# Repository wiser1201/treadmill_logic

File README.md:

# Description

This project replaces the entire logic/control section of a broken treadmill with a custom-designed **STM32** microcontroller-based control system. The power electronic part of the original board stayed intact, but the control MCU and interface electronics were redesigned to restore full functionality and improve usability. Firmware is written in **C** using **HAL** library and register access when needed.

# Hardware

### Components

- **Power PCB:** Reused robust power part of the original board;
- **Logic PCB:** Designed board that contains low-voltage supply + control logic;
- **Interface PCB:** Contains three buttons, and LCD 16x2;
- **MCU:** STM32 F103C6T6;

### Architecture

System uses phase angle control topology. The original power board contains an optocoupler that triggers a triac driving the 220 VAC power rail. After each zero-cross event, the triac naturally turns off; the moment at which it is fired determines what portion of each AC half-wave reaches the motor.

The logic PCB generates a zero-cross pulse using a transformer (13 VAC), rectifier, and an optocoupler. When the AC waveform rises above the LED threshold (~1.2 V), the optocoupler produces a clean pulse that marks each zero-crossing. STM32 receives this pulse, TIM1 in one pulse slave mode starts counting a delay automatically, and then, in the end of the delay, fires a short trigger pulse to the power-stage optocoupler, which in turn fires the main triac.

Motor speed is closed-loop controlled. The PID controller adjusts delay of TIM1 based on the current speed, calculated via RPM and a belt length. If current speed lower than target, PID decreases TIM1 delay, that gives more power to the triac. And vice versa.

# Software

### Architecture

Almost all software is divided into two layers: driver and application. 

- **Driver layer.** Low level code related to peripheral configuration, peripheral initialization.

- **Application layer.** Code, that's not related or not only related to peripherals. Software that built on top of the drivers, and corresponds to one specific use.

Some modules (such as simple Buttons or Buzzer) are too small to justify a strict driver/application separation. In these cases, the functionality is implemented in a single combined module to keep the code clean and avoid unnecessary fragmentation.

### Main loop

The main loop coordinates the system's high-level tasks: motion control, fault monitoring, button handling**, **buzzer control, and LCD updates:

- **motion.** Executes the PID-based speed control described earlier, updating the phase-angle delay according to the current RPM feedback.
- **fault_check.** Monitors critical runtime conditions. It ensures that tim3, hall sensor and motion control work correctly.
- **buttons_handler.** Polls the user interface buttons (Start/Stop, Speed+, Speed–), debounces input, passes information to the system module.
- **buzzer.** Non-blocking audible feedback system.
- **LCD.** Periodically updates the 16×2 LCD with four metrics: Calories (C), Speed (S), Time (T), and Distance (D). The update routine is optimized to refresh only changed fields.

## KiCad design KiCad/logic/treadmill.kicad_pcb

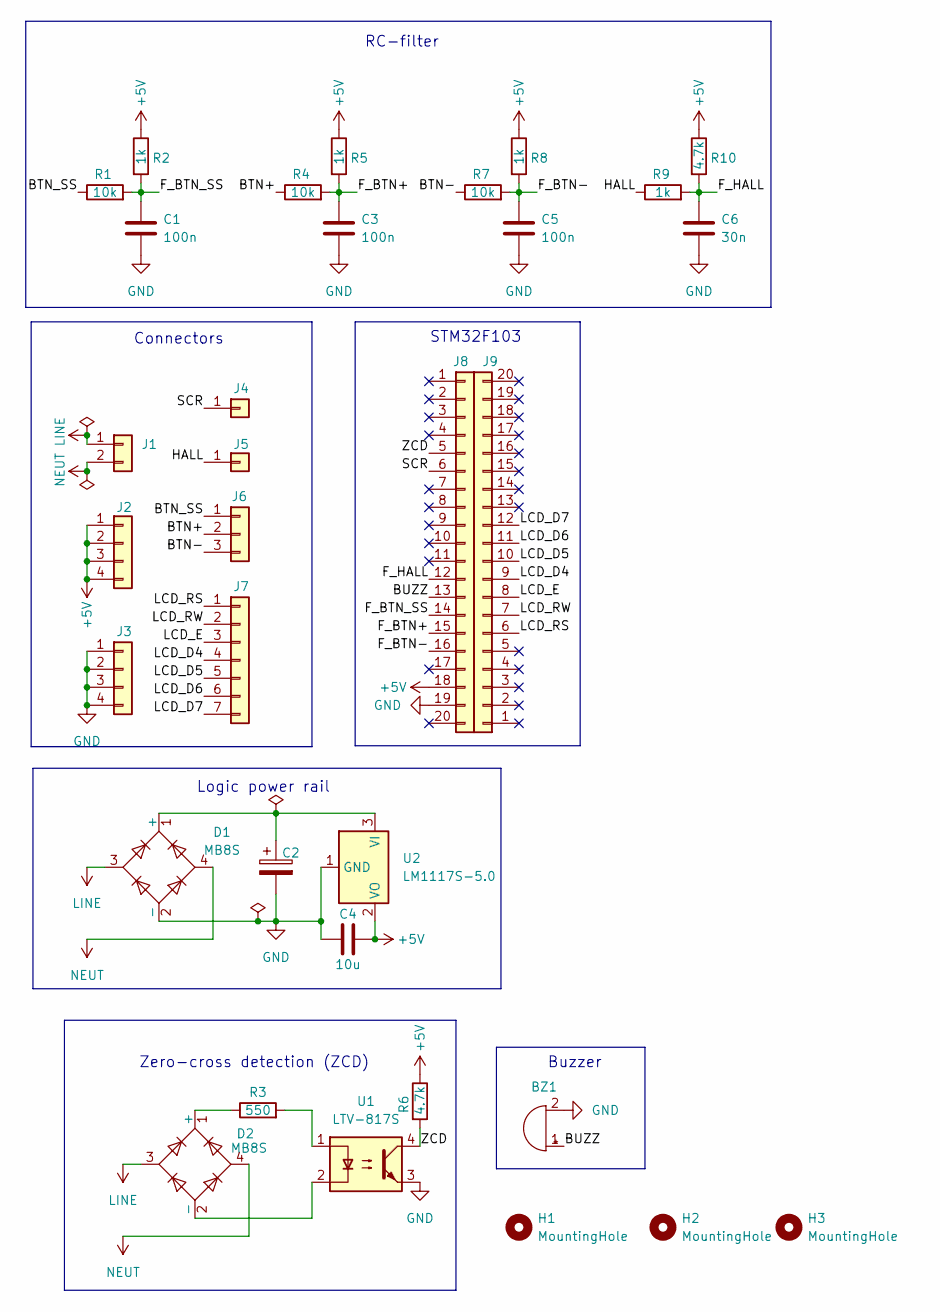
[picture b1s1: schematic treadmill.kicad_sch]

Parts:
BZ1: Buzzer; Buzzer_12x9.5RM7.6
C1, C3, C5: 100n; C_0805_2012Metric
C2: C_Polarized; CP_Radial_D13.0mm_P7.50mm
C4: 10u; C_0805_2012Metric
C6: 30n; C_0805_2012Metric
D1, D2: MB8S; OnSemi_751EP_SOIC-4_3.9x4.725mm_P2.54mm
H1, H2, H3: MountingHole; MountingHole_3.2mm_M3
J1: AC; TerminalBlock_Phoenix_MKDS-1,5-2_1x02_P5.00mm_Horizontal
J2: +5V; PinHeader_1x04_P2.54mm_Vertical
J3: GND; PinHeader_1x04_P2.54mm_Vertical
J4: SCR_01x01; PinHeader_1x01_P2.54mm_Vertical
J5: HALL_01x01; PinHeader_1x01_P2.54mm_Vertical
J6: BTN_01x03; PinSocket_1x03_P2.54mm_Vertical
J7: LCD_01x07; PinSocket_1x07_P2.54mm_Vertical
J8: MCU-1; PinSocket_1x20_P2.54mm_Vertical
J9: MCU-2; PinSocket_1x20_P2.54mm_Vertical
R1, R4, R7: 10k; R_0805_2012Metric
R2, R5, R8, R9: 1k; R_0805_2012Metric
R3: 550; R_2010_5025Metric
R6, R10: 4.7k; R_0805_2012Metric
U1: LTV-817S; SMDIP-4_W9.53mm
U2: LM1117S-5.0; SOT-223-3_TabPin2

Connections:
+5V: C4.2, J2.1, J2.2, J2.3, J2.4, J8.18, R2.1, R5.1, R6.1, R8.1, R10.1, U2.2 (VO)
/BTN+: J6.2, R4.1
/BTN-: J6.3, R7.1
/BTN_SS: J6.1, R1.1
/BUZZ: BZ1.1 (+), J8.13
/F_BTN+: C3.1, J8.15, R4.2, R5.2
/F_BTN-: C5.1, J8.16, R7.2, R8.2
/F_BTN_SS: C1.1, J8.14, R1.2, R2.2
/F_HALL: C6.1, J8.12, R9.2, R10.2
/HALL: J5.1, R9.1
/LCD_D4: J7.4, J9.9
/LCD_D5: J7.5, J9.10
/LCD_D6: J7.6, J9.11
/LCD_D7: J7.7, J9.12
/LCD_E: J7.3, J9.8
/LCD_RS: J7.1, J9.6
/LCD_RW: J7.2, J9.7
/SCR: J4.1, J8.6
/ZCD: J8.5, R6.2, U1.4
GND: BZ1.2 (-), C1.2, C2.2, C3.2, C4.1, C5.2, C6.2, D1.2 (-), J3.1, J3.2, J3.3, J3.4, J8.19, U1.3, U2.1 (GND)
LINE: D1.3, D2.3, J1.1
NEUT: D1.4, D2.4, J1.2
unnamed: C2.1, D1.1 (+), U2.3 (VI)
unnamed: D2.1 (+), R3.1
unnamed: D2.2 (-), U1.2
unnamed: R3.2, U1.1

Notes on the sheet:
Buzzer
Zero-cross detection (ZCD)
Logic power rail
Connectors
RC-filter
STM32F103

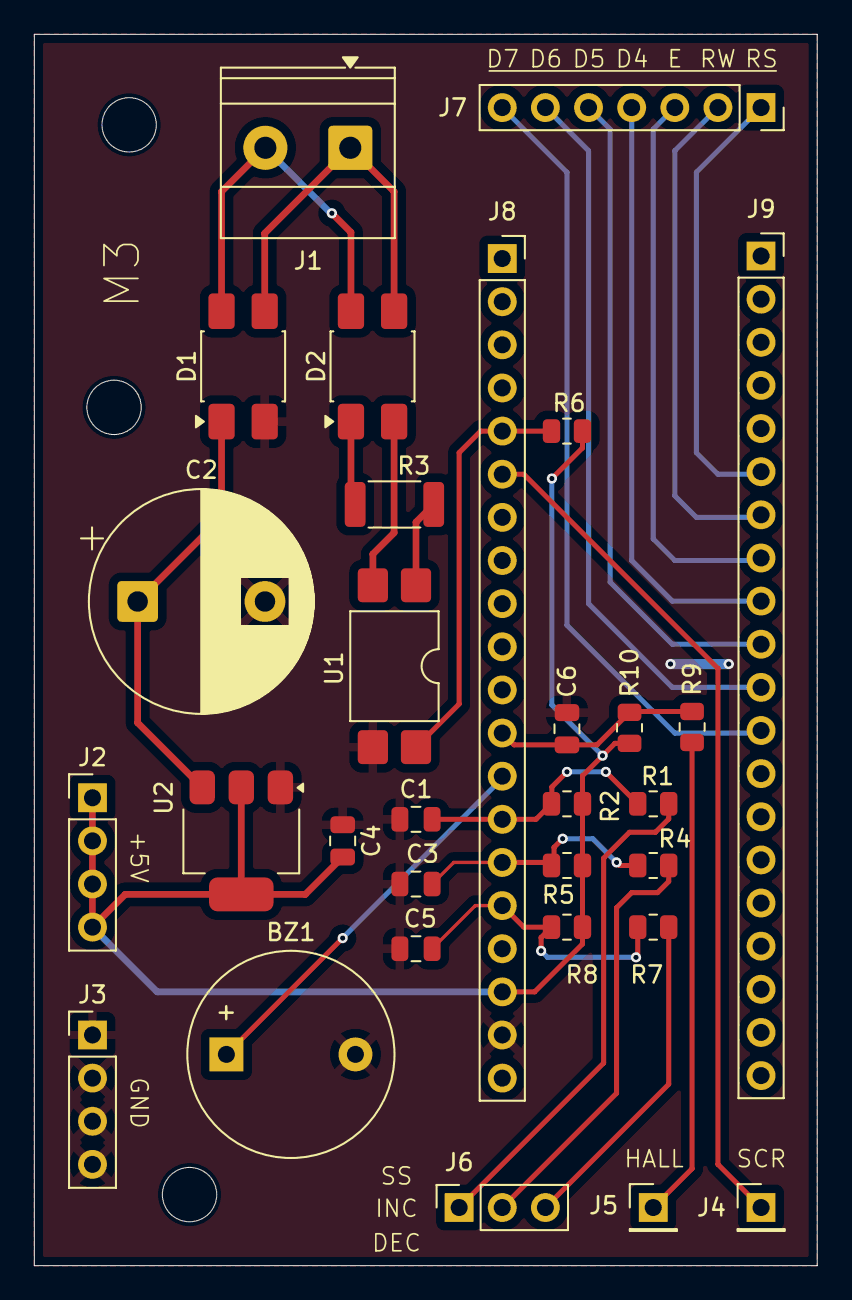
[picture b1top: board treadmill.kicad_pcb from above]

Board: 2 copper layers, 46.1 x 72.5 mm, 33 parts (0 on the bottom side), 26 nets.

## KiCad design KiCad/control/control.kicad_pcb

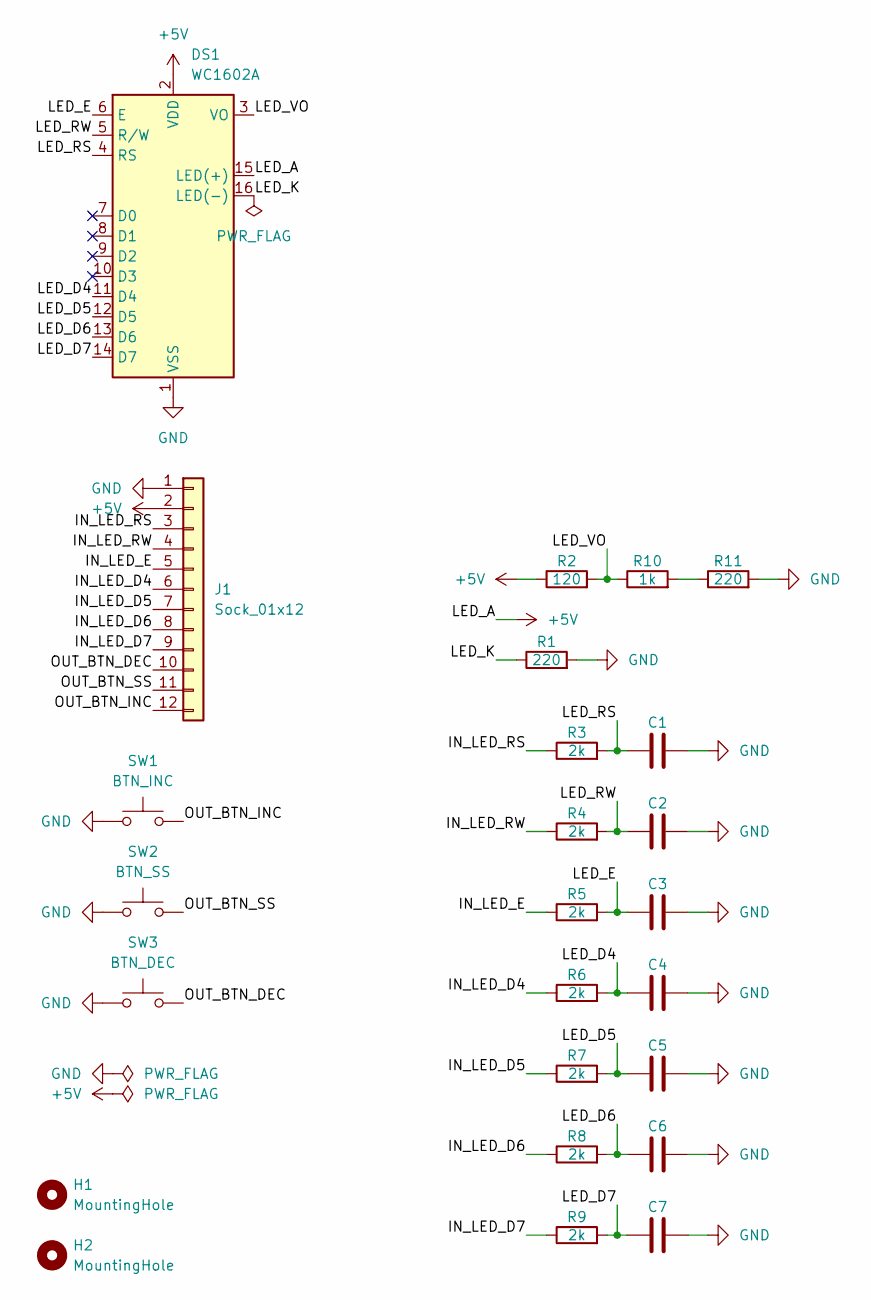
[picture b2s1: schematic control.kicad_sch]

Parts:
C1, C2, C3, C4, C5, C6, C7: 1n; C_0805_2012Metric
DS1: WC1602A
H1, H2: MountingHole; MountingHole_2.7mm
J1: Sock_01x12; PinSocket_1x12_P2.54mm_Vertical
R1, R11: 220; R_1210_3225Metric
R2: 120; R_1210_3225Metric
R3, R4, R5, R6, R7, R8, R9: 2k; R_0805_2012Metric
R10: 1k; R_1210_3225Metric
SW1: BTN_INC; SW_PUSH-12mm
SW2: BTN_SS; SW_PUSH-12mm
SW3: BTN_DEC; SW_PUSH-12mm

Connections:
+5V: DS1.2 (VDD), DS1.15 (LED(+)), J1.2, R2.1
/IN_LED_D4: J1.6, R6.1
/IN_LED_D5: J1.7, R7.1
/IN_LED_D6: J1.8, R8.1
/IN_LED_D7: J1.9, R9.1
/IN_LED_E: J1.5, R5.1
/IN_LED_RS: J1.3, R3.1
/IN_LED_RW: J1.4, R4.1
/LED_D4: C4.2, DS1.11 (D4), R6.2
/LED_D5: C5.2, DS1.12 (D5), R7.2
/LED_D6: C6.2, DS1.13 (D6), R8.2
/LED_D7: C7.2, DS1.14 (D7), R9.2
/LED_E: C3.2, DS1.6 (E), R5.2
/LED_K: DS1.16 (LED(-)), R1.1
/LED_RS: C1.2, DS1.4 (RS), R3.2
/LED_RW: C2.2, DS1.5 (R/W), R4.2
/LED_VO: DS1.3 (VO), R2.2, R10.1
/OUT_BTN_DEC: J1.10, SW3.2
/OUT_BTN_INC: J1.12, SW1.2
/OUT_BTN_SS: J1.11, SW2.2
GND: C1.1, C2.1, C3.1, C4.1, C5.1, C6.1, C7.1, DS1.1 (VSS), J1.1, R1.2, R11.2, SW1.1, SW2.1, SW3.1
unnamed: R10.2, R11.1

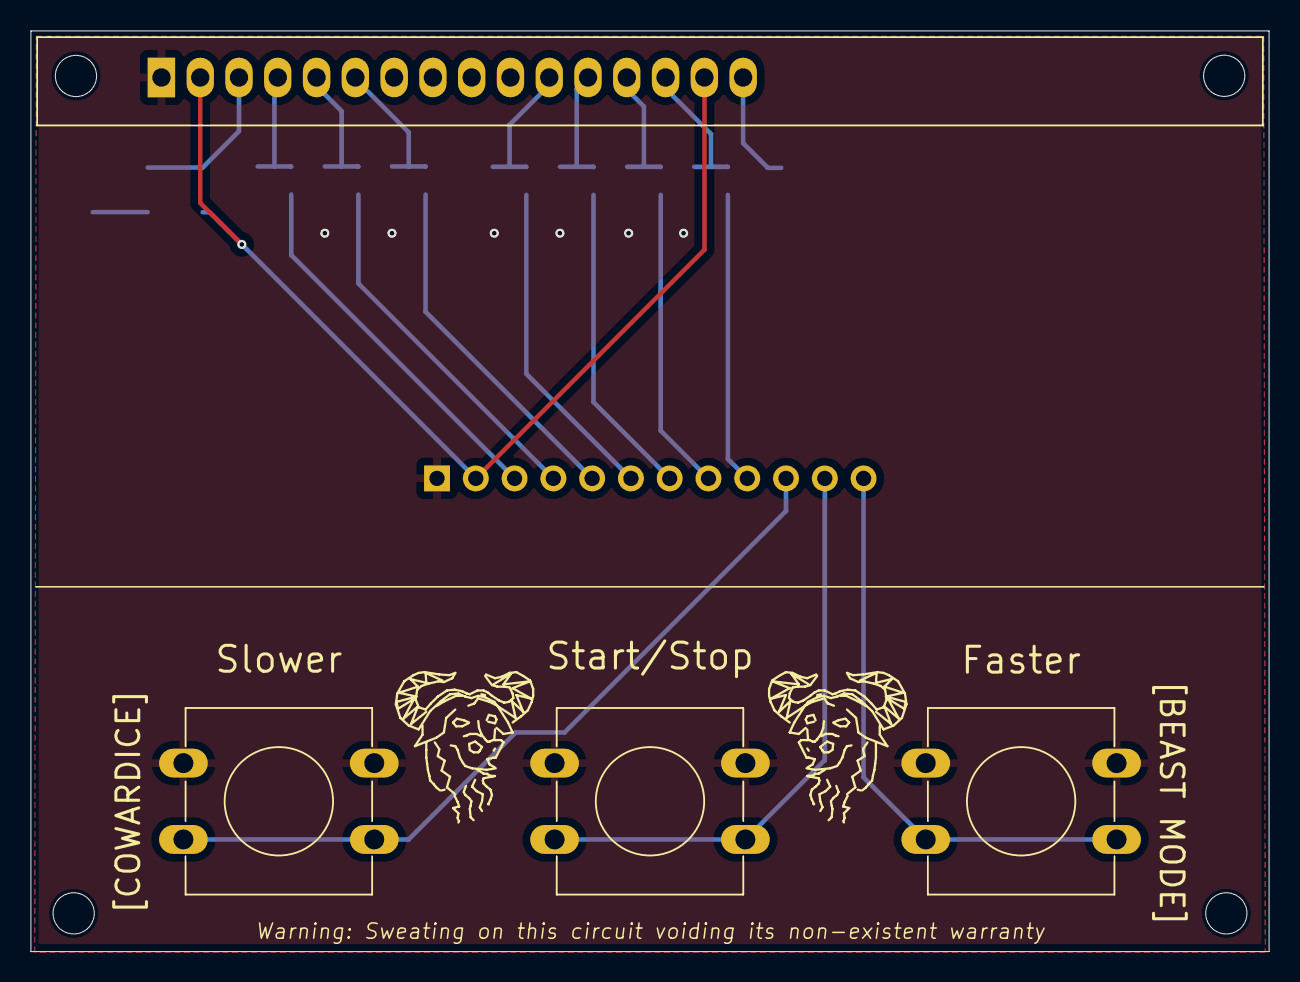
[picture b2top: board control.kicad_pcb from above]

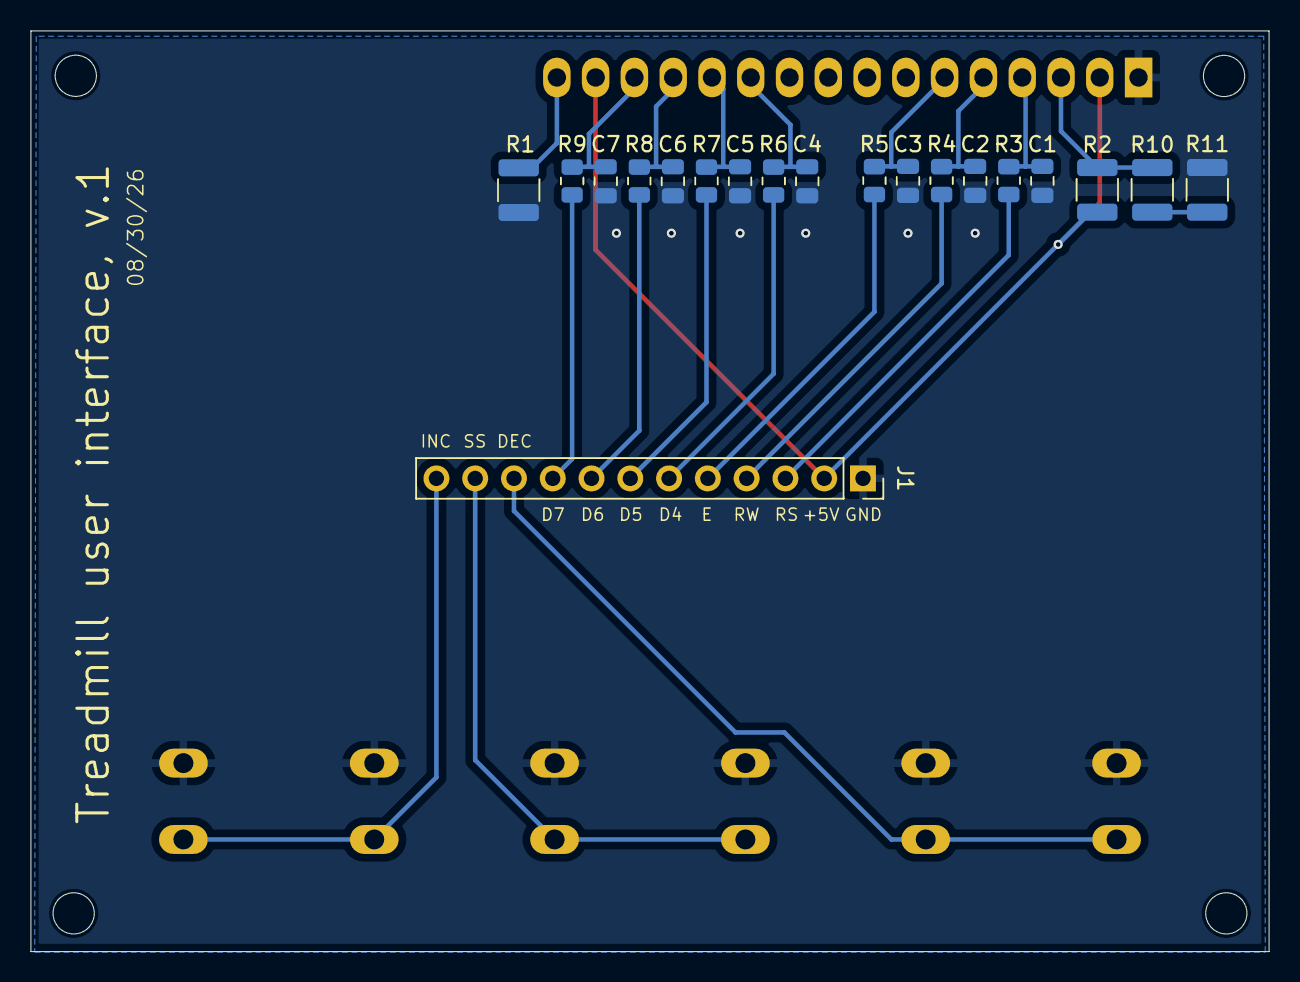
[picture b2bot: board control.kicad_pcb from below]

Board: 2 copper layers, 81.1 x 60.3 mm, 25 parts (19 on the bottom side), 22 nets.

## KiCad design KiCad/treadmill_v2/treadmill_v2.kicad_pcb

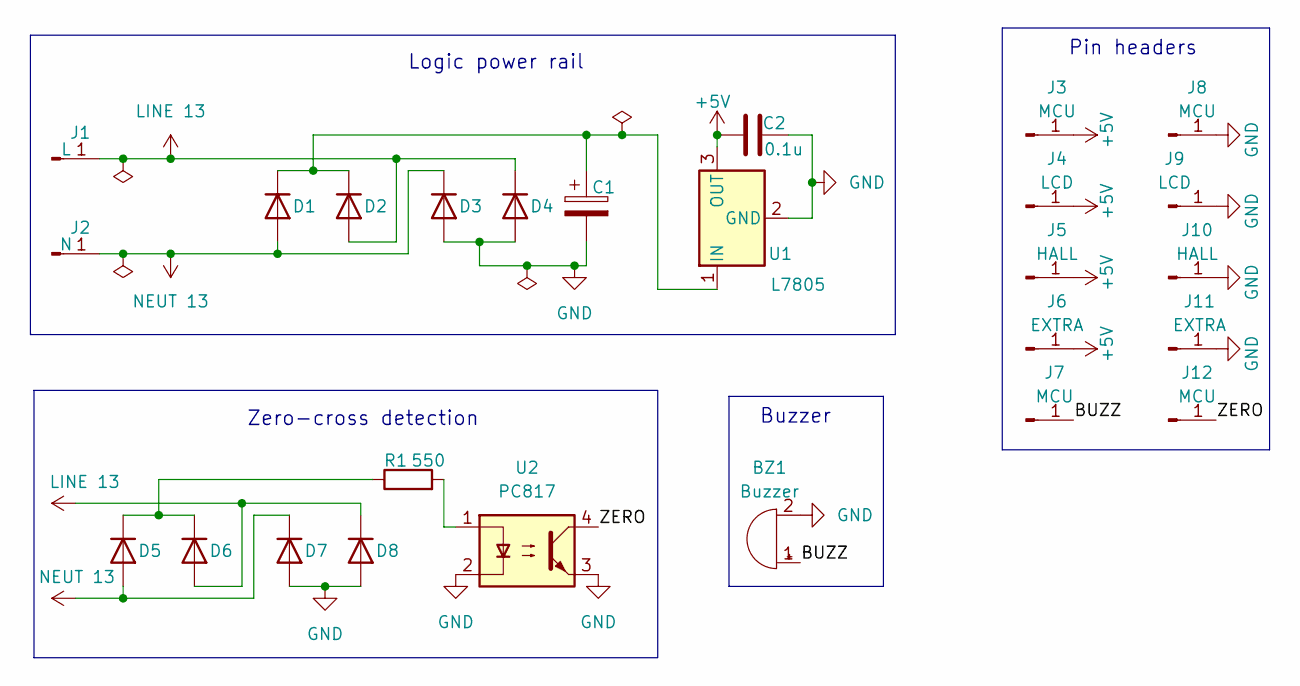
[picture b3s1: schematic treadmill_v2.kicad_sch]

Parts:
BZ1: Buzzer; Buzzer_12x9.5RM7.6
C1: 1000u; CP_Radial_D13.0mm_P2.50mm
C2: 0.1u; C_Disc_D6.0mm_W4.4mm_P5.00mm
D1, D2, D3, D4, D5, D6, D7, D8: 1N4007; D_DO-41_SOD81_P10.16mm_Horizontal
J1: L; Spade
J2: N; Spade
J3, J7, J8, J12: MCU; SolderWire-0.1sqmm_1x01_D0.4mm_OD1mm
J4, J9: LCD; SolderWire-0.1sqmm_1x01_D0.4mm_OD1mm
J5, J10: HALL; SolderWire-0.1sqmm_1x01_D0.4mm_OD1mm
J6, J11: EXTRA; SolderWire-0.1sqmm_1x01_D0.4mm_OD1mm
R1: 550; R_Axial_DIN0207_L6.3mm_D2.5mm_P7.62mm_Horizontal
U1: L7805; TO-220-3_Vertical
U2: PC817; DIP-4_W7.62mm

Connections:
+5V: C2.1, J3.1, J4.1, J5.1, J6.1, U1.3 (OUT)
/BUZZ: BZ1.1 (+), J7.1
/ZERO: J12.1, U2.4
GND: BZ1.2 (-), C1.2, C2.2, D3.2 (A), D4.2 (A), D7.2 (A), D8.2 (A), J8.1, J9.1, J10.1, J11.1, U1.2 (GND), U2.2, U2.3
LINE 13: D2.2 (A), D4.1 (K), D6.2 (A), D8.1 (K), J1.1
NEUT 13: D1.2 (A), D3.1 (K), D5.2 (A), D7.1 (K), J2.1
unnamed: C1.1, D1.1 (K), D2.1 (K), U1.1 (IN)
unnamed: D5.1 (K), D6.1 (K), R1.1
unnamed: R1.2, U2.1

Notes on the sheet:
Logic power rail
Pin headers
Zero-cross detection
Buzzer

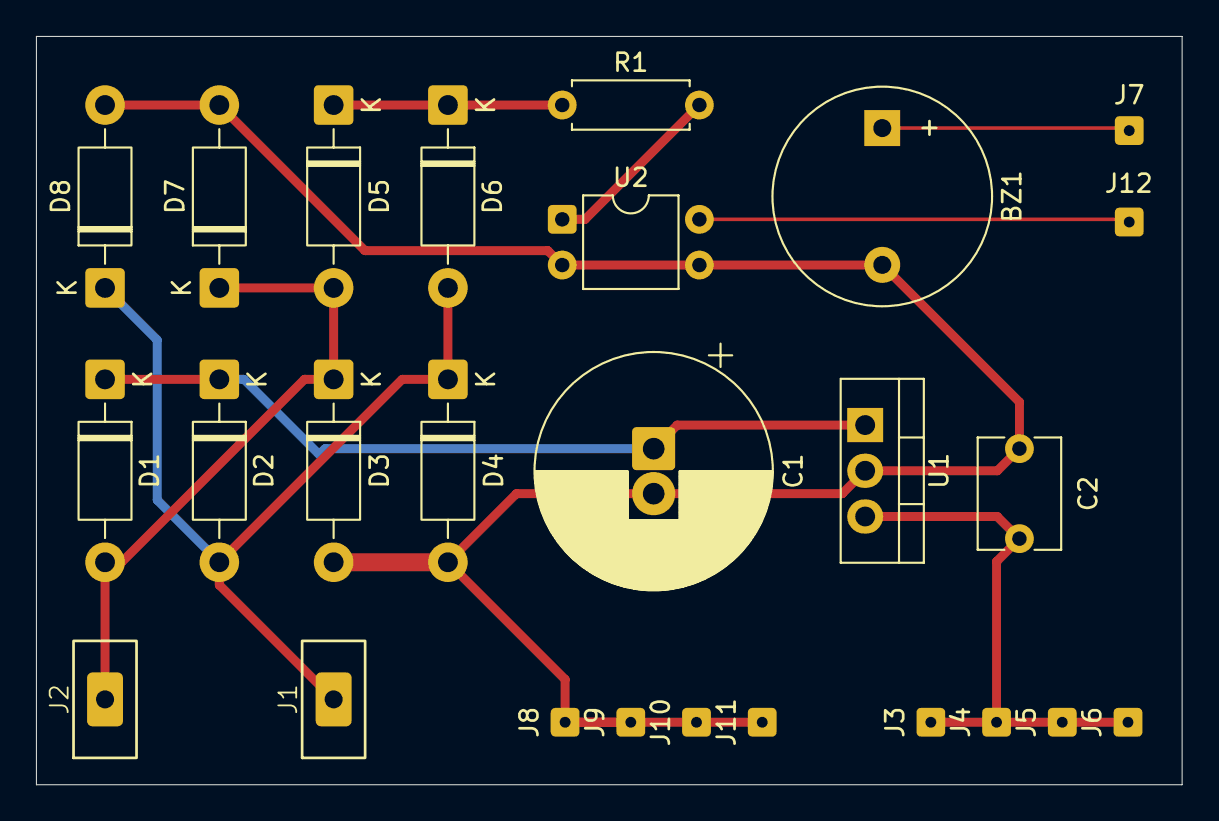
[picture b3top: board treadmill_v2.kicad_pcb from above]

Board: 2 copper layers, 63.6 x 41.6 mm, 26 parts (0 on the bottom side), 9 nets.

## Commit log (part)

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2025-11-11 Init commit MCU code contains nothing, scheme and pcb has been already done.
2025-11-11 Addition: tim1 tim1 logic consists of basic init/start/stop/reset. One pulse mode. Tested. By default OC disabled (CCR = period + 1 while mode is PWM2, so disabled).
2025-11-11 Feat: tim1: get/set period app needs this feature. setPeriod automatically sets CCR channel as period - TIMER1_PULSE_US.
2025-11-11 Addition: files from treadmill_v1 Most of the files are ok, none need to edit. But there is two that have to be chaned. system and motion.
2025-11-16 Release Stable tested version. Speed regulation a little bit floating when error becomes small. But in general, good job.
2025-11-22 docs: readme, comments
2025-11-30 fix: timer formula Pervious formula worked just fine. But from a sanity perspective, it was a nonsense.
2026-02-19 debug: tim3 definitions
